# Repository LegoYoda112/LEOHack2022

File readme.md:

# LEOHack 2022
This is a repository for all the code written for the LEOHack 2022 competition run by ICRS and ICSS. This contains both the code to run the actual satellites and a simulator.

## Getting set up

We highly recommend forking the repository, as this is the most efficient way to get access to the code while still maintaining version control and a link to the original (so you can get updates during the event). See https://docs.github.com/en/get-started/quickstart/fork-a-repo for a quick tutorial on how to do that.

A python 3.8 install is required, if you do not have this installed, install from: https://www.python.org/downloads/release/python-386/

A video version of the next few steps is here: https://youtu.be/1hygeTHZObU If you run into any issues, message the help channel on teams and @ Thomas.

Clone the repo onto your local machine ([GitHub Desktop](https://desktop.github.com/) is recommended) and open it up in your coding editor of choice, [VS Code](https://code.visualstudio.com/) is always a fan favorite.

Next we will install a virtual environment and required packages. Pipenv will handle this for us. Don't forget to run these commands in the LEOHack folder.
``` 
pip install pipenv
pipenv install
```
If you prefer to use a different package manager, a list of required packages is as follows: `protobuf coloredlogs numpy meshcat argparse wxpython`.

To check if everything works, spin up the simulator using 
```
pipenv run python ./software/simulator/sim_gui.py
``` 
from the root LEOHack folder.

## Writing your first sat controller

Jump into `team/first_controller.md` and take it from there!

## What's contained here
For competition participants; you will not need to worry about most of the files in this repo (anything in `hardware` or `software`) unless you are interested in looking at how some of the back end stuff works.

`hardware` contains PCB designs for the pi pico breakout boards.

`software` contains all software elements.
- `base_control` contains code to communicate between the base station and the satellite
- `low_level` can be deleted
- `micropython` contains the embedded python code that runs on the sats
- `msgs` defines protobuf messages that are used to pass information between base station and fatalities
- `sat_control` contains both the team written control code and the comms code that runs on the satellite itself
- `simulator` contains all code to run the simulator
- `tests` contains old code

`team` contains code and scripts for each team to interact with
- `team_controller.py` is where teams will write their custom control code

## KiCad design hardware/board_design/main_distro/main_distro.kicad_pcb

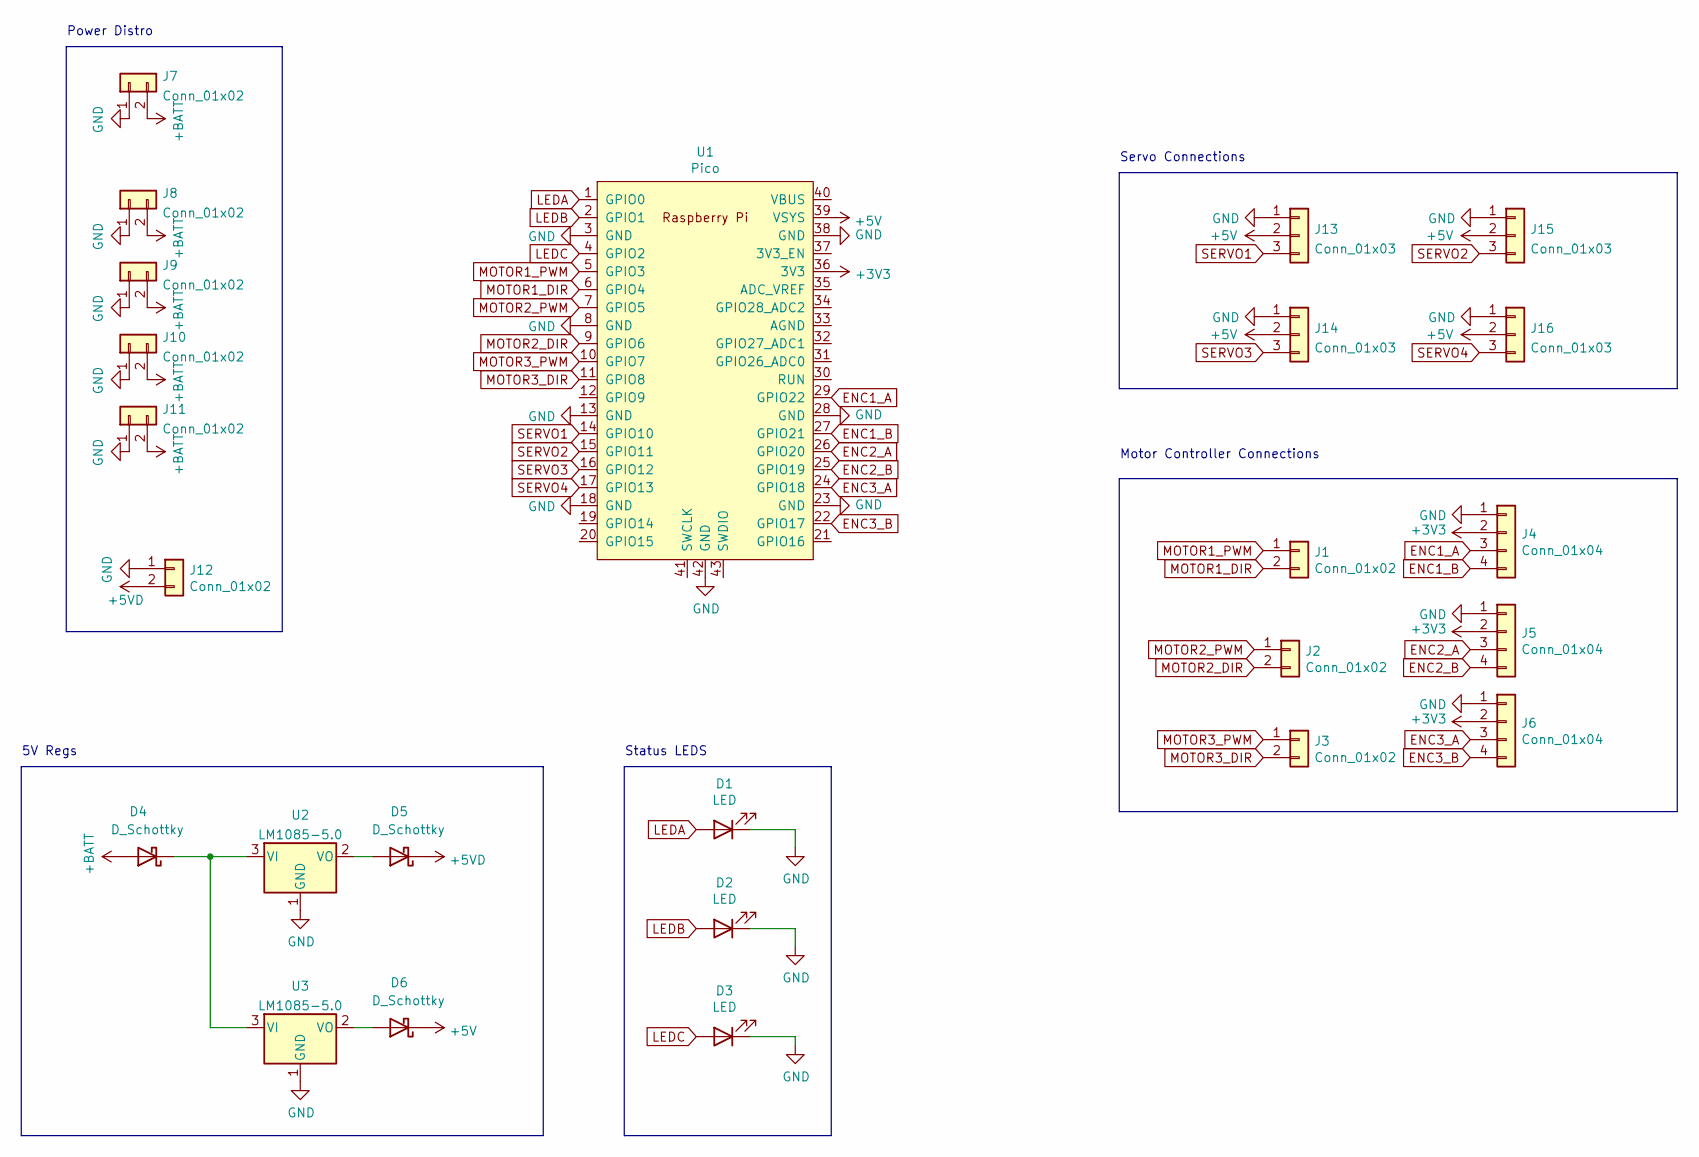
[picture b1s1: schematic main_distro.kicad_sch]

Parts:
D1, D2, D3: LED; LED_0805_2012Metric_Pad1.15x1.40mm_HandSolder
D4, D5, D6: D_Schottky; D_SMB_Handsoldering
J1, J2, J3, J12: Conn_01x02; JST_XH_B2B-XH-A_1x02_P2.50mm_Vertical
J4, J5, J6: Conn_01x04; JST_XH_B4B-XH-A_1x04_P2.50mm_Vertical
J7: Conn_01x02; AMASS_XT30U-M_1x02_P5.0mm_Vertical
J8, J9, J10, J11: Conn_01x02; AMASS_XT30U-F_1x02_P5.0mm_Vertical
J13, J14, J15, J16: Conn_01x03; PinHeader_1x03_P2.54mm_Vertical
U1: Pico; RPi_Pico_SMD_TH
U2, U3: LM1085-5.0; TO-263-2

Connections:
+3V3: J4.2, J5.2, J6.2, U1.36 (3V3)
+5V: D6.1 (K), J13.2, J14.2, J15.2, J16.2, U1.39 (VSYS)
+5VD: D5.1 (K), J12.2
+BATT: D4.2 (A), J7.2, J8.2, J9.2, J10.2, J11.2
ENC1_A: J4.3, U1.29 (GPIO22)
ENC1_B: J4.4, U1.27 (GPIO21)
ENC2_A: J5.3, U1.26 (GPIO20)
ENC2_B: J5.4, U1.25 (GPIO19)
ENC3_A: J6.3, U1.24 (GPIO18)
ENC3_B: J6.4, U1.22 (GPIO17)
GND: D1.1 (K), D2.1 (K), D3.1 (K), J4.1, J5.1, J6.1, J7.1, J8.1, J9.1, J10.1, J11.1, J12.1, J13.1, J14.1, J15.1, J16.1, U1.3 (GND), U1.8 (GND), U1.13 (GND), U1.18 (GND), U1.23 (GND), U1.28 (GND), U1.38 (GND), U1.42 (GND), U2.1 (GND), U3.1 (GND)
LEDA: D1.2 (A), U1.1 (GPIO0)
LEDB: D2.2 (A), U1.2 (GPIO1)
LEDC: D3.2 (A), U1.4 (GPIO2)
MOTOR1_DIR: J1.2, U1.6 (GPIO4)
MOTOR1_PWM: J1.1, U1.5 (GPIO3)
MOTOR2_DIR: J2.2, U1.9 (GPIO6)
MOTOR2_PWM: J2.1, U1.7 (GPIO5)
MOTOR3_DIR: J3.2, U1.11 (GPIO8)
MOTOR3_PWM: J3.1, U1.10 (GPIO7)
unnamed: D4.1 (K), U2.3 (VI), U3.3 (VI)
unnamed: D5.2 (A), U2.2 (VO)
unnamed: D6.2 (A), U3.2 (VO)
SERVO1: J13.3, U1.14 (GPIO10)
SERVO2: J15.3, U1.15 (GPIO11)
SERVO3: J14.3, U1.16 (GPIO12)
SERVO4: J16.3, U1.17 (GPIO13)

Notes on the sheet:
5V Regs
Status LEDS
Motor Controller Connections
Power Distro
Servo Connections

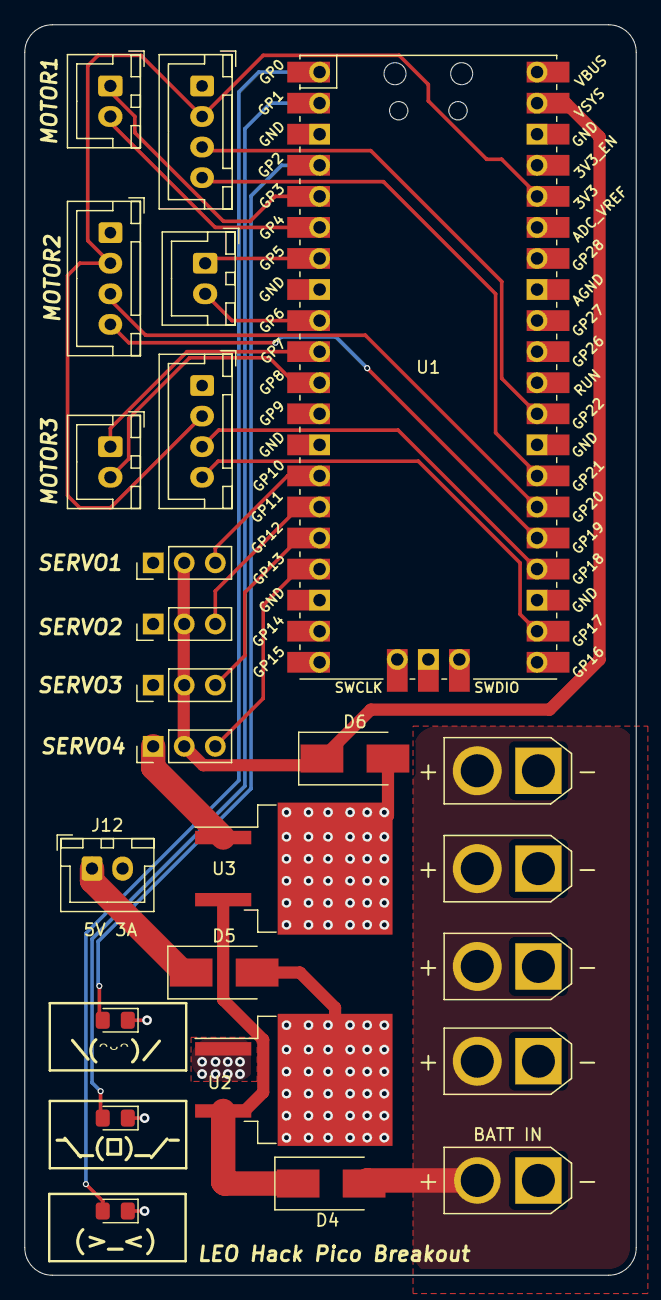
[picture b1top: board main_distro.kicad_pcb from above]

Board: 2 copper layers, 50.0 x 102.2 mm, 25 parts (0 on the bottom side), 27 nets.

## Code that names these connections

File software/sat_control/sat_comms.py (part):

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        self.global_sat_vel.CopyFrom(zero_vel)

        zero_servo = sat_msgs.ServoStates()
        zero_servo.servo1 = 0
        zero_servo.servo2 = 0
        zero_servo.servo3 = 0

        self.cmd_vel_and_servo(zero_vel, zero_servo)

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
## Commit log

2021-09-20 Initial testing, very messy
2021-10-19 Added heartbeat
2021-11-11 Getting caught up on untracked changes
2021-11-12 Added sat_control class
2021-11-12 Remote control sat side code
2021-11-13 Remove control testing
2021-11-13 Remote control
2021-11-13 Restructure
2021-11-14 More restructure and basic sim framework
2021-12-28 Redid protobuf file and started drafting the sat controller interface
2021-12-29 Updated the sat controller interface
2021-12-29 Added logging into team controller
2021-12-29 Basic sat controller running, thinking about simplifying it a bunch
2021-12-29 Started work on new simulation interface
2021-12-31 Updated schematic for main board
2021-12-31 Added servo connections
2021-12-31 Added PCB layout
2022-01-01 Traces ran
2022-01-07 Updated for JLC order
2022-01-07 Added minimal sim thread controls (they work???)
2022-01-15 Removed .obj from gitignore
2022-01-24 Added micropython code
2022-01-29 Added basic 2D sim backend
2022-01-29 Added elapsed time into sim
2022-02-07 Initial sat control rewrite and micropython updates
2022-02-09 Begun work rewriting sat_coms
2022-02-09 Updates sat comms and base control
2022-02-09 Got basestation <=> sat comms running
2022-02-09 Sim improvements
2022-02-09 Changed sim no gui run message slightly
2022-02-09 Started writing documentation
2022-02-10 Added auto host name
2022-02-10 Added micropython loader
2022-02-10 Added closed loop velocity control
2022-02-10 Updates from getting robot running
2022-02-11 Basic aruco detector
2022-02-11 Added OAK-D marker tracking
2022-02-11 Added tracking thread
2022-02-11 Tracking!
2022-02-11 Last min updates haha
2022-02-12 Updated sim instructions
2022-02-12 Updated sim
2022-02-12 Updated first controller and docking spec
2022-02-12 Typo fixing
2022-02-12 Files from sat_control
    files updated
2022-02-12 Updated spelling and servos
2022-02-12 target positions
2022-02-12 merged nabs and added impulse
2022-02-12 Challenge 1
2022-02-12 nothing
2022-02-12 something
2022-02-12 current
2022-02-12 more stuff
2022-02-12 something again
2022-02-13 okay
2022-02-18 Comp updates
